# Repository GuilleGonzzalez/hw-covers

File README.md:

# Covers

## Description

'Covers' is a PCB designed to control x5 covers with 10 relays and automatize it with [Home Assistant](https://www.home-assistant.io/).

Firmware used in this device is [tasmota](https://tasmota.github.io/docs/), an open source firmware for ESP devices.

## Power supply

The board is powered with a 230VAC power supply.

## Microprocessor

Espressif [ESP32-S3-WROOM](https://www.espressif.com/en/products/modules) module.

## LEDs

2 user LEDs. Functionality to define

## Relay Mode

**Circuit Safe**
* Relay1: ON/OFF
* Relay2: UP/DOWN

A RC snubber has been added for all relays to absorb voltage spikes

## Tasmota config

An example template will be uploaded when configured.

## Pin assignment

| PIN     | Func    |
| ------- | ------- |
| OUT1    | GPIO12  |
| DIR1    | GPIO11  |
| OUT2    | GPIO14  |
| DIR2    | GPIO13  |
| OUT3    | GPIO47  |
| DIR3    | GPIO21  |
| OUT4    | GPIO18  |
| DIR4    | GPIO08  |
| OUT5    | GPIO16  |
| DIR5    | GPIO17  |
| 1IN1    | GPIO09  |
| 1IN2    | GPIO10  |
| 2IN1    | GPIO19  |
| 2IN2    | GPIO20  |
| 3IN1    | GPIO40  |
| 3IN2    | GPIO39  |
| 4IN1    | GPIO42  |
| 4IN2    | GPIO41  |
| 5IN1    | GPIO01  |
| 5IN2    | GPIO02  |
| IR      | GPIO06  |
| LED1    | GPIO15  |
| LED2    | GPIO07  |
| EXT1    | GPIO04  |
| EXT2    | GPIO05  |

## Enclosure

* Custom made.

## Changelog

All notable changes to this project will be documented in this section.

The format is based on [Keep a Changelog](https://keepachangelog.com/en/1.0.0/)

### [Unreleased]

### [2.1.0] - 2026-03-09

Fix some 2.0.0 rev issues

#### Added

* Add RC-snubbers values
* Add IR base resistor
* Add via stiching in regulator for power disipation

#### Fixed

* Fix L/N label text
* Isolate 230V AC lines from 5V DC lines

#### Changed

* Change relays transistor base from 1k to 470ohm

### [2.0.0] - 2026-03-08

Solved relay issue

#### Added

* Add RC snubbers
* Add schematic hierarchicals sheets

#### Fixed

* Change relays from 5A to 10A
* Change relay config to hardware-safe (output and direction) using form-C relays

#### Changed

* Change input resistor from 10k to 1k5
* Change ESP pin assignment

### [1.1.0] - 2025-02-28

Bug fixes

#### Added

* IR LED resistor value calculated: 180ohm

#### Fixed

* Relay NO/NC bug
* 1N4448W diode package fixed: SOD-123

#### Changed

* Better relays: 5A instead 3A, better pinout for clearance, thiner footprint
* HiLink symbol
* Rounded corners
* Components size: R/C 0603 instead 0402
* Inputs/outputs order: from left to right 1-5 in both cases

### [1.0.0] - 2025-02-05

First release

#### Added

* x5 covers

[Unreleased]: https://github.com/GuilleGonzzalez/hw-covers
[1.0.0]: https://github.com/GuilleGonzzalez/hw-covers/tree/v1.0.0
[1.1.0]: https://github.com/GuilleGonzzalez/hw-covers/tree/v1.1.0
[2.0.0]: https://github.com/GuilleGonzzalez/hw-covers/tree/v2.0.0
[2.1.0]: https://github.com/GuilleGonzzalez/hw-covers/tree/v2.1.0

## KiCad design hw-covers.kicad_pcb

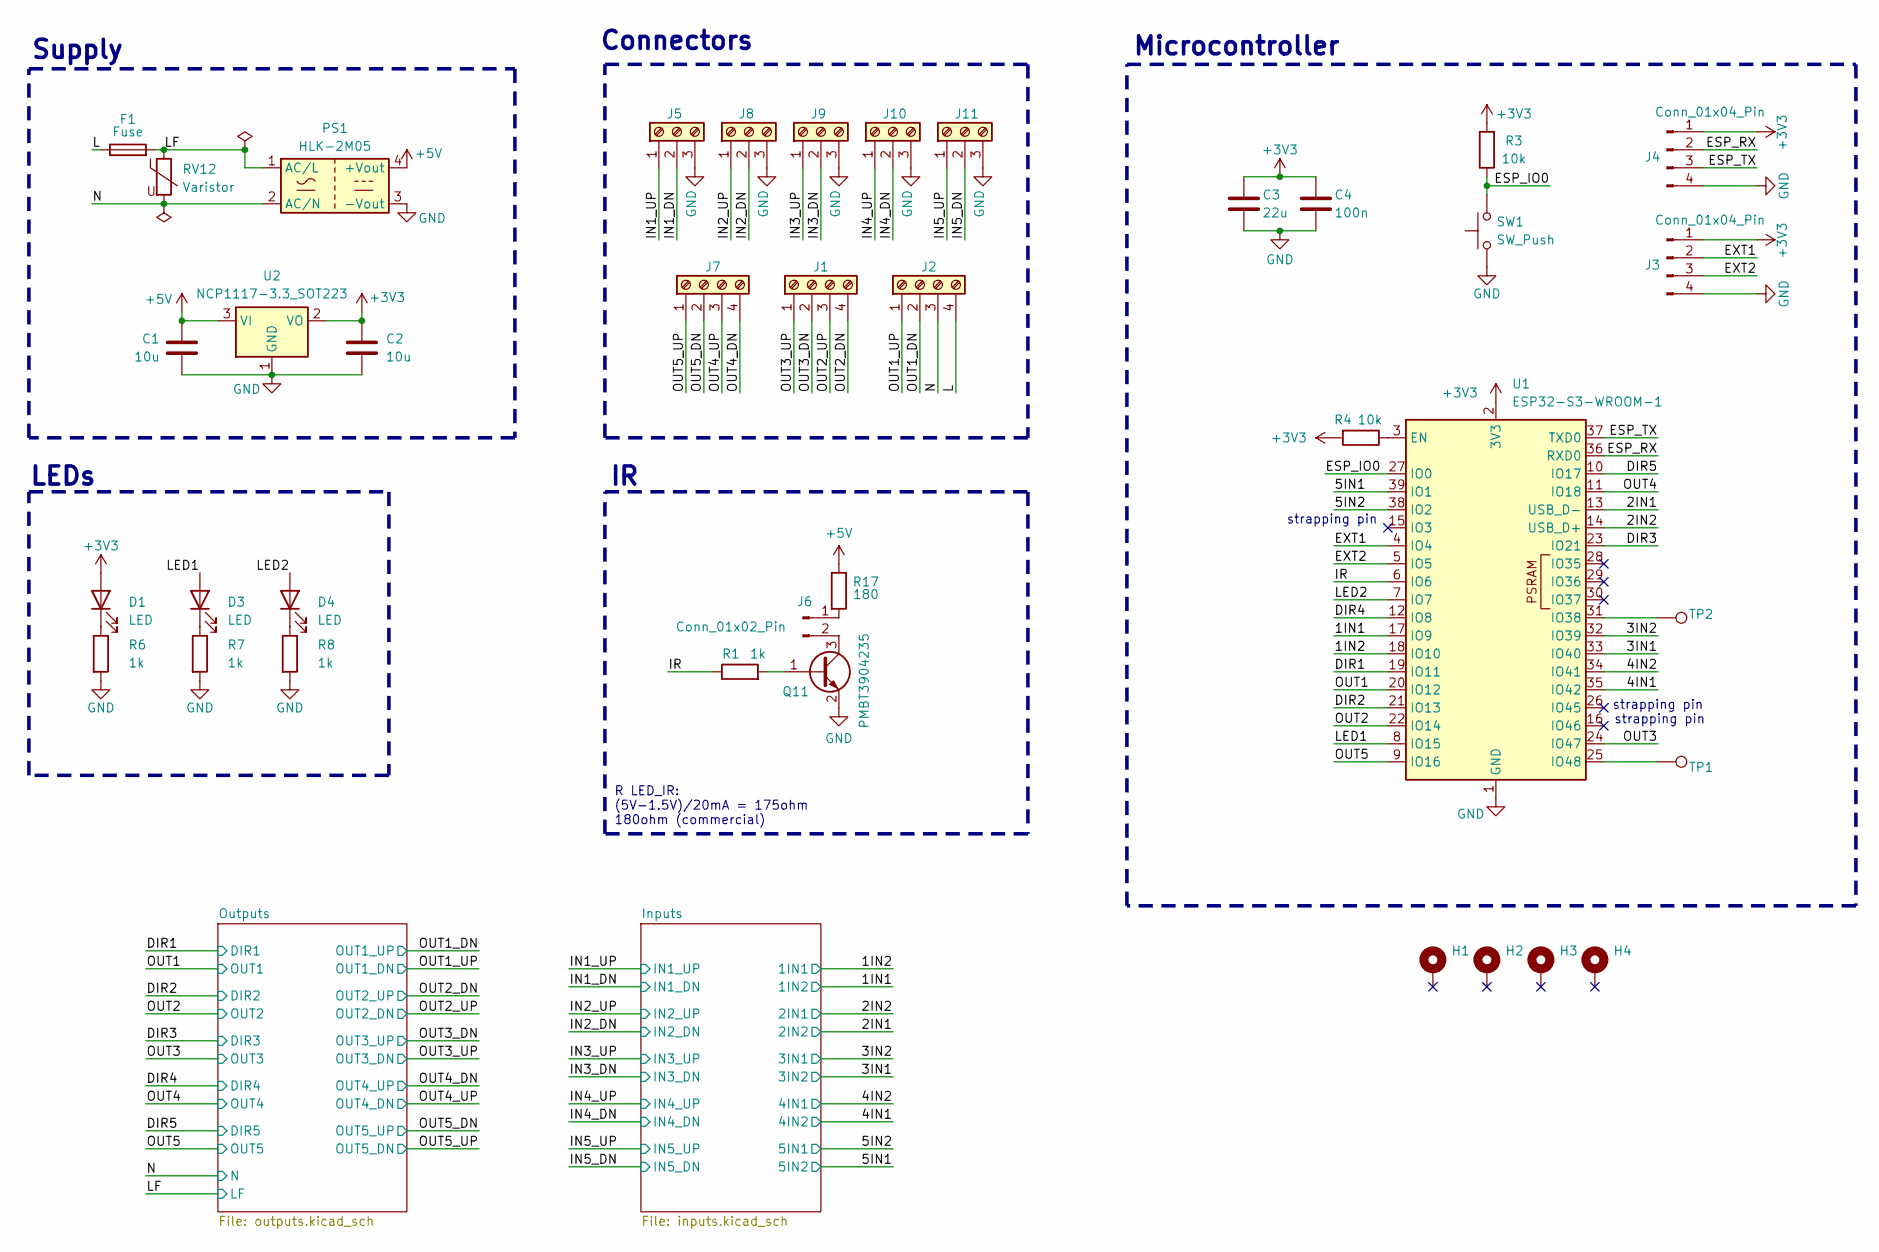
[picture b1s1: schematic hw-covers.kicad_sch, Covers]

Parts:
C1, C2: 10u; C_0805_2012Metric
C3: 22u; C_0805_2012Metric
C4: 100n; C_0603_1608Metric
D1, D3, D4: LED; LED_0603_1608Metric
F1: Fuse; Fuse_2512_6332Metric
H1, H2, H3, H4: MountingHole_3.2mm_M3_Pad
J1, J2, J7: Screw_Terminal_01x04; PhoenixContact_MSTBA_2,5_4-G-5,08_1x04_P5.08mm_Horizontal
J3, J4: Conn_01x04_Pin; PinHeader_1x04_P2.54mm_Vertical
J5, J8, J9, J10, J11: Screw_Terminal_01x03; PhoenixContact_MC_1,5_3-G-3.81_1x03_P3.81mm_Horizontal
J6: Conn_01x02_Pin; PinHeader_1x02_P2.54mm_Vertical
PS1: HLK-2M05; Converter_ACDC_Hi-Link_HLK-2Mxx
Q11: PMBT3904235; SOT-23; Manufacturer_PN PMBT3904,235
R1, R6, R7, R8: 1k; R_0603_1608Metric
R3, R4: 10k; R_0603_1608Metric
R17: 180; R_0603_1608Metric
RV12: Varistor; RV_Disc_D12mm_W4.5mm_P7.5mm
SW1: SW_Push; SW_SPST_PTS810
TP1, TP2: TestPoint; TestPoint_Pad_D1.5mm
U1: ESP32-S3-WROOM-1
U2: NCP1117-3.3_SOT223; SOT-223-3_TabPin2

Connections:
+3V3: C2.1, C3.1, C4.1, D1.2 (A), J3.1, J4.1, R3.2, R4.2, U1.2 (3V3), U2.2 (VO); also elsewhere on the board
+5V: C1.1, PS1.4 (+Vout), R17.1, U2.3 (VI); also elsewhere on the board
/1IN1: U1.17 (IO9); also elsewhere on the board
/1IN2: U1.18 (IO10); also elsewhere on the board
/2IN1: U1.13 (USB_D-); also elsewhere on the board
/2IN2: U1.14 (USB_D+); also elsewhere on the board
/3IN1: U1.33 (IO40); also elsewhere on the board
/3IN2: U1.32 (IO39); also elsewhere on the board
/4IN1: U1.35 (IO42); also elsewhere on the board
/4IN2: U1.34 (IO41); also elsewhere on the board
/5IN1: U1.39 (IO1); also elsewhere on the board
/5IN2: U1.38 (IO2); also elsewhere on the board
/DIR1: U1.19 (IO11); also elsewhere on the board
/DIR2: U1.21 (IO13); also elsewhere on the board
/DIR3: U1.23 (IO21); also elsewhere on the board
/DIR4: U1.12 (IO8); also elsewhere on the board
/DIR5: U1.10 (IO17); also elsewhere on the board
/ESP_IO0: R3.1, SW1.2, U1.27 (IO0)
/ESP_RX: J4.2, U1.36 (RXD0)
/ESP_TX: J4.3, U1.37 (TXD0)
/EXT1: J3.2, U1.4 (IO4)
/EXT2: J3.3, U1.5 (IO5)
/IN1_DN: J5.2; also elsewhere on the board
/IN1_UP: J5.1; also elsewhere on the board
/IN2_DN: J8.2; also elsewhere on the board
/IN2_UP: J8.1; also elsewhere on the board
/IN3_DN: J9.2; also elsewhere on the board
/IN3_UP: J9.1; also elsewhere on the board
/IN4_DN: J10.2; also elsewhere on the board
/IN4_UP: J10.1; also elsewhere on the board
/IN5_DN: J11.2; also elsewhere on the board
/IN5_UP: J11.1; also elsewhere on the board
/IR: R1.1, U1.6 (IO6)
/L: F1.1, J2.4
/LED1: D3.2 (A), U1.8 (IO15)
/LED2: D4.2 (A), U1.7 (IO7)
/LF: F1.2, PS1.1 (AC/L), RV12.1; also elsewhere on the board
/N: J2.3, PS1.2 (AC/N), RV12.2; also elsewhere on the board
/OUT1: U1.20 (IO12); also elsewhere on the board
/OUT1_DN: J2.2; also elsewhere on the board
/OUT1_UP: J2.1; also elsewhere on the board
/OUT2: U1.22 (IO14); also elsewhere on the board
/OUT2_DN: J1.4; also elsewhere on the board
/OUT2_UP: J1.3; also elsewhere on the board
/OUT3: U1.24 (IO47); also elsewhere on the board
/OUT3_DN: J1.2; also elsewhere on the board
/OUT3_UP: J1.1; also elsewhere on the board
/OUT4: U1.11 (IO18); also elsewhere on the board
/OUT4_DN: J7.4; also elsewhere on the board
/OUT4_UP: J7.3; also elsewhere on the board
/OUT5: U1.9 (IO16); also elsewhere on the board
/OUT5_DN: J7.2; also elsewhere on the board
/OUT5_UP: J7.1; also elsewhere on the board
GND: C1.2, C2.2, C3.2, C4.2, J3.4, J4.4, J5.3, J8.3, J9.3, J10.3, J11.3, PS1.3 (-Vout), Q11.2, R6.2, R7.2, R8.2, SW1.1, U1.1 (GND), U1.40 (GND), U1.41 (GND), U2.1 (GND); also elsewhere on the board
unnamed: D1.1 (K), R6.1
unnamed: D3.1 (K), R7.1
unnamed: D4.1 (K), R8.1
unnamed: J6.1, R17.2
unnamed: J6.2, Q11.3
unnamed: Q11.1, R1.2
unnamed: R4.1, U1.3 (EN)
unnamed: TP2.1, U1.31 (IO38)
unnamed: TP1.1, U1.25 (IO48)

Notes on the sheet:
Microcontroller
strapping pin
Supply
Connectors
R LED_IR: (5V-1.5V)/20mA = 175ohm 180ohm (commercial)
LEDs

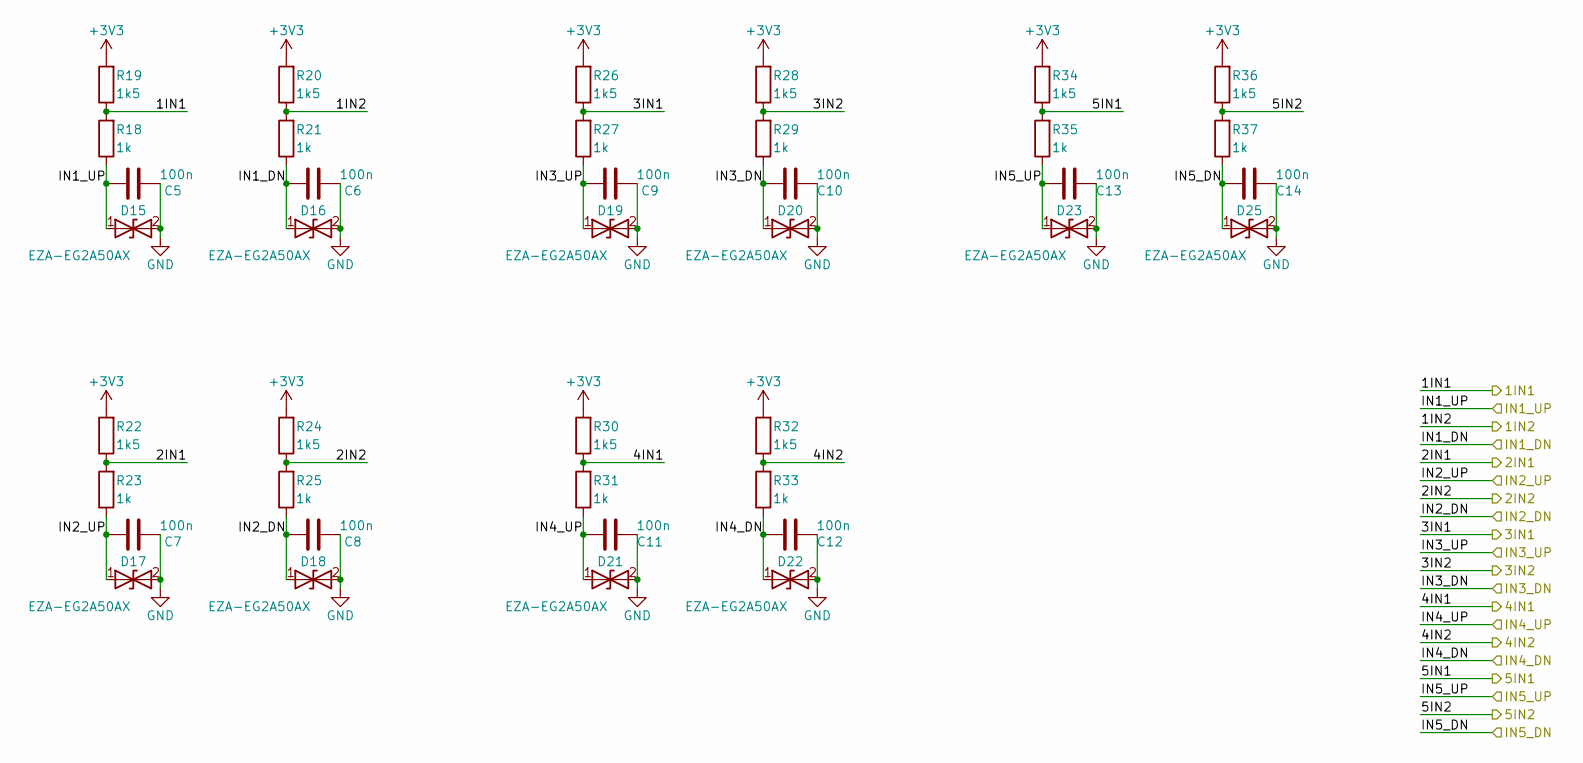
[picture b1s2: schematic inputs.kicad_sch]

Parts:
C5, C6, C7, C8, C9, C10, C11, C12, C13, C14: 100n; C_0603_1608Metric
D15, D16, D17, D18, D19, D20, D21, D22, D23, D25: EZA-EG2A50AX; EZAEG2A50AX; Manufacturer_Part_Number EZA-EG2A50AX; Mouser Part Number 667-EZA-EG2A50AX
R18, R21, R23, R25, R27, R29, R31, R33, R35, R37: 1k; R_0603_1608Metric
R19, R20, R22, R24, R26, R28, R30, R32, R34, R36: 1k5; R_0603_1608Metric

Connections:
+3V3: R19.2, R20.2, R22.2, R24.2, R26.2, R28.2, R30.2, R32.2, R34.2, R36.2; also elsewhere on the board
/1IN1: R20.1, R21.2; also elsewhere on the board
/1IN2: R18.2, R19.1; also elsewhere on the board
/2IN1: R24.1, R25.2; also elsewhere on the board
/2IN2: R22.1, R23.2; also elsewhere on the board
/3IN1: R28.1, R29.2; also elsewhere on the board
/3IN2: R26.1, R27.2; also elsewhere on the board
/4IN1: R32.1, R33.2; also elsewhere on the board
/4IN2: R30.1, R31.2; also elsewhere on the board
/5IN1: R36.1, R37.2; also elsewhere on the board
/5IN2: R34.1, R35.2; also elsewhere on the board
/IN1_DN: C6.1, D16.1 (A1), R21.1; also elsewhere on the board
/IN1_UP: C5.1, D15.1 (A1), R18.1; also elsewhere on the board
/IN2_DN: C8.1, D18.1 (A1), R25.1; also elsewhere on the board
/IN2_UP: C7.1, D17.1 (A1), R23.1; also elsewhere on the board
/IN3_DN: C10.1, D20.1 (A1), R29.1; also elsewhere on the board
/IN3_UP: C9.1, D19.1 (A1), R27.1; also elsewhere on the board
/IN4_DN: C12.1, D22.1 (A1), R33.1; also elsewhere on the board
/IN4_UP: C11.1, D21.1 (A1), R31.1; also elsewhere on the board
/IN5_DN: C14.1, D25.1 (A1), R37.1; also elsewhere on the board
/IN5_UP: C13.1, D23.1 (A1), R35.1; also elsewhere on the board
GND: C5.2, C6.2, C7.2, C8.2, C9.2, C10.2, C11.2, C12.2, C13.2, C14.2, D15.2 (A2), D16.2 (A2), D17.2 (A2), D18.2 (A2), D19.2 (A2), D20.2 (A2), D21.2 (A2), D22.2 (A2), D23.2 (A2), D25.2 (A2); also elsewhere on the board

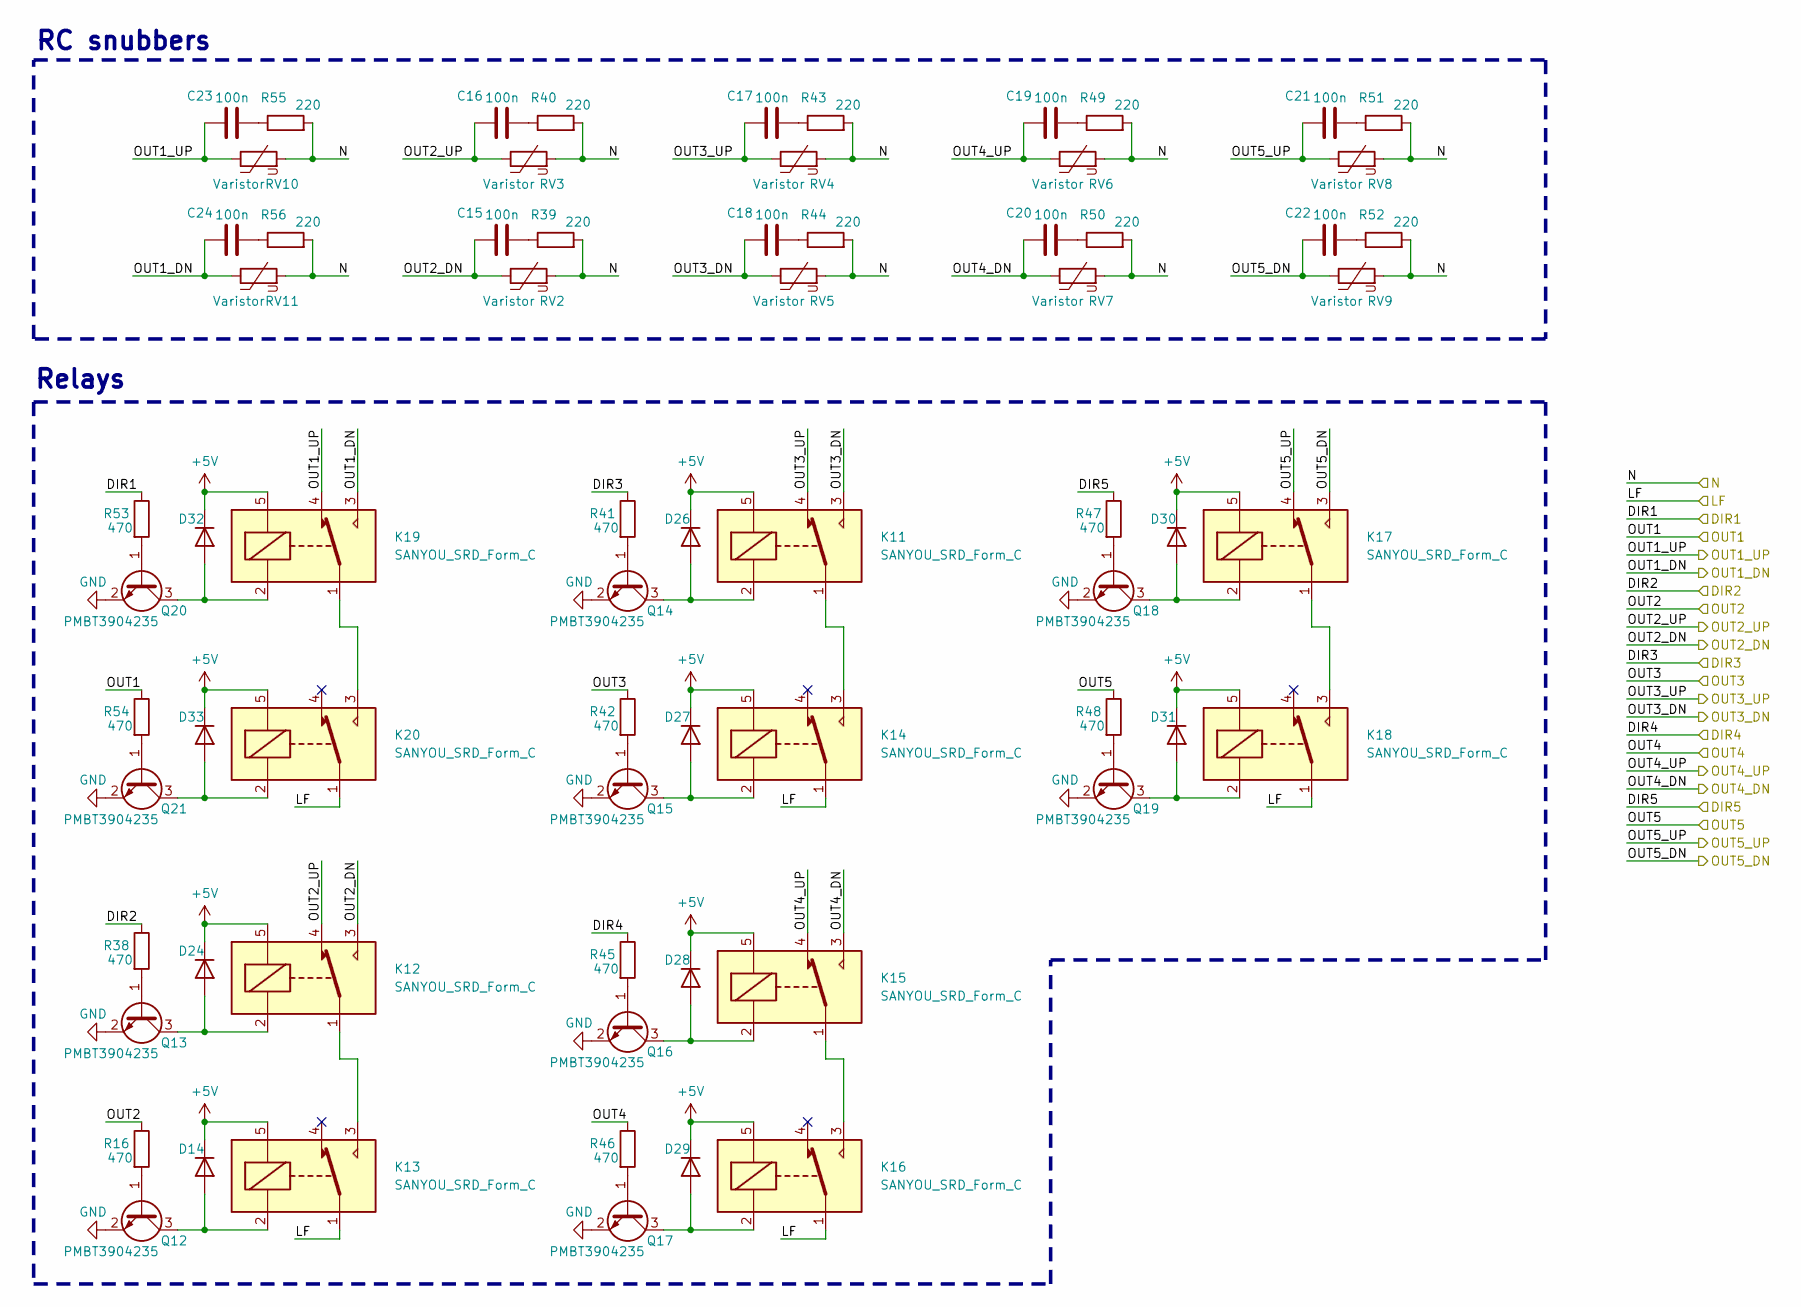
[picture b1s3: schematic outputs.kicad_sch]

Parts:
C15, C16, C17, C18, C19, C20, C21, C22, C23, C24: 100n; C_Rect_L18.0mm_W7.0mm_P15.00mm_FKS3_FKP3
D14, D24, D26, D27, D28, D29, D30, D31, D32, D33: 1N4448W; D_SOD-123
K11, K12, K13, K14, K15, K16, K17, K18, K19, K20: SANYOU_SRD_Form_C; Relay_SPDT_SANYOU_SRD_Series_Form_C
Q12, Q13, Q14, Q15, Q16, Q17, Q18, Q19, Q20, Q21: PMBT3904235; SOT-23; Manufacturer_PN PMBT3904,235
R16, R38, R41, R42, R45, R46, R47, R48, R53, R54: 470; R_0603_1608Metric
R39, R40, R43, R44, R49, R50, R51, R52, R55, R56: 220; R_Axial_DIN0614_L14.3mm_D5.7mm_P15.24mm_Horizontal
RV2, RV3, RV4, RV5, RV6, RV7, RV8, RV9, RV10, RV11: Varistor; RV_Disc_D12mm_W3.9mm_P7.5mm

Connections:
+5V: D14.1 (K), D24.1 (K), D26.1 (K), D27.1 (K), D28.1 (K), D29.1 (K), D30.1 (K), D31.1 (K), D32.1 (K), D33.1 (K), K11.5, K12.5, K13.5, K14.5, K15.5, K16.5, K17.5, K18.5, K19.5, K20.5; also elsewhere on the board
/DIR1: R53.1; also elsewhere on the board
/DIR2: R38.1; also elsewhere on the board
/DIR3: R41.1; also elsewhere on the board
/DIR4: R45.1; also elsewhere on the board
/DIR5: R47.1; also elsewhere on the board
/LF: K13.1, K14.1, K16.1, K18.1, K20.1; also elsewhere on the board
/N: R39.2, R40.2, R43.2, R44.2, R49.2, R50.2, R51.2, R52.2, R55.2, R56.2, RV2.2, RV3.2, RV4.2, RV5.2, RV6.2, RV7.2, RV8.2, RV9.2, RV10.2, RV11.2; also elsewhere on the board
/OUT1: R54.1; also elsewhere on the board
/OUT1_DN: C23.1, K19.4, RV10.1; also elsewhere on the board
/OUT1_UP: C24.1, K19.3, RV11.1; also elsewhere on the board
/OUT2: R16.1; also elsewhere on the board
/OUT2_DN: C16.1, K12.4, RV3.1; also elsewhere on the board
/OUT2_UP: C15.1, K12.3, RV2.1; also elsewhere on the board
/OUT3: R42.1; also elsewhere on the board
/OUT3_DN: C17.1, K11.4, RV4.1; also elsewhere on the board
/OUT3_UP: C18.1, K11.3, RV5.1; also elsewhere on the board
/OUT4: R46.1; also elsewhere on the board
/OUT4_DN: C19.1, K15.4, RV6.1; also elsewhere on the board
/OUT4_UP: C20.1, K15.3, RV7.1; also elsewhere on the board
/OUT5: R48.1; also elsewhere on the board
/OUT5_DN: C21.1, K17.4, RV8.1; also elsewhere on the board
/OUT5_UP: C22.1, K17.3, RV9.1; also elsewhere on the board
GND: Q12.2, Q13.2, Q14.2, Q15.2, Q16.2, Q17.2, Q18.2, Q19.2, Q20.2, Q21.2; also elsewhere on the board
unnamed: C15.2, R39.1
unnamed: C16.2, R40.1
unnamed: C17.2, R43.1
unnamed: C18.2, R44.1
unnamed: C19.2, R49.1
unnamed: C20.2, R50.1
unnamed: C21.2, R51.1
unnamed: C22.2, R52.1
unnamed: C23.2, R55.1
unnamed: C24.2, R56.1
unnamed: D14.2 (A), K13.2, Q12.3
unnamed: D24.2 (A), K12.2, Q13.3
unnamed: D26.2 (A), K11.2, Q14.3
unnamed: D27.2 (A), K14.2, Q15.3
unnamed: D28.2 (A), K15.2, Q16.3
unnamed: D29.2 (A), K16.2, Q17.3
unnamed: D30.2 (A), K17.2, Q18.3
unnamed: D31.2 (A), K18.2, Q19.3
unnamed: D32.2 (A), K19.2, Q20.3
unnamed: D33.2 (A), K20.2, Q21.3
unnamed: K11.1, K14.3
unnamed: K12.1, K13.3
unnamed: K15.1, K16.3
unnamed: K17.1, K18.3
unnamed: K19.1, K20.3
unnamed: Q12.1, R16.2
unnamed: Q13.1, R38.2
unnamed: Q14.1, R41.2
unnamed: Q15.1, R42.2
unnamed: Q16.1, R45.2
unnamed: Q17.1, R46.2
unnamed: Q18.1, R47.2
unnamed: Q19.1, R48.2
unnamed: Q20.1, R53.2
unnamed: Q21.1, R54.2

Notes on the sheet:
Relays
RC snubbers

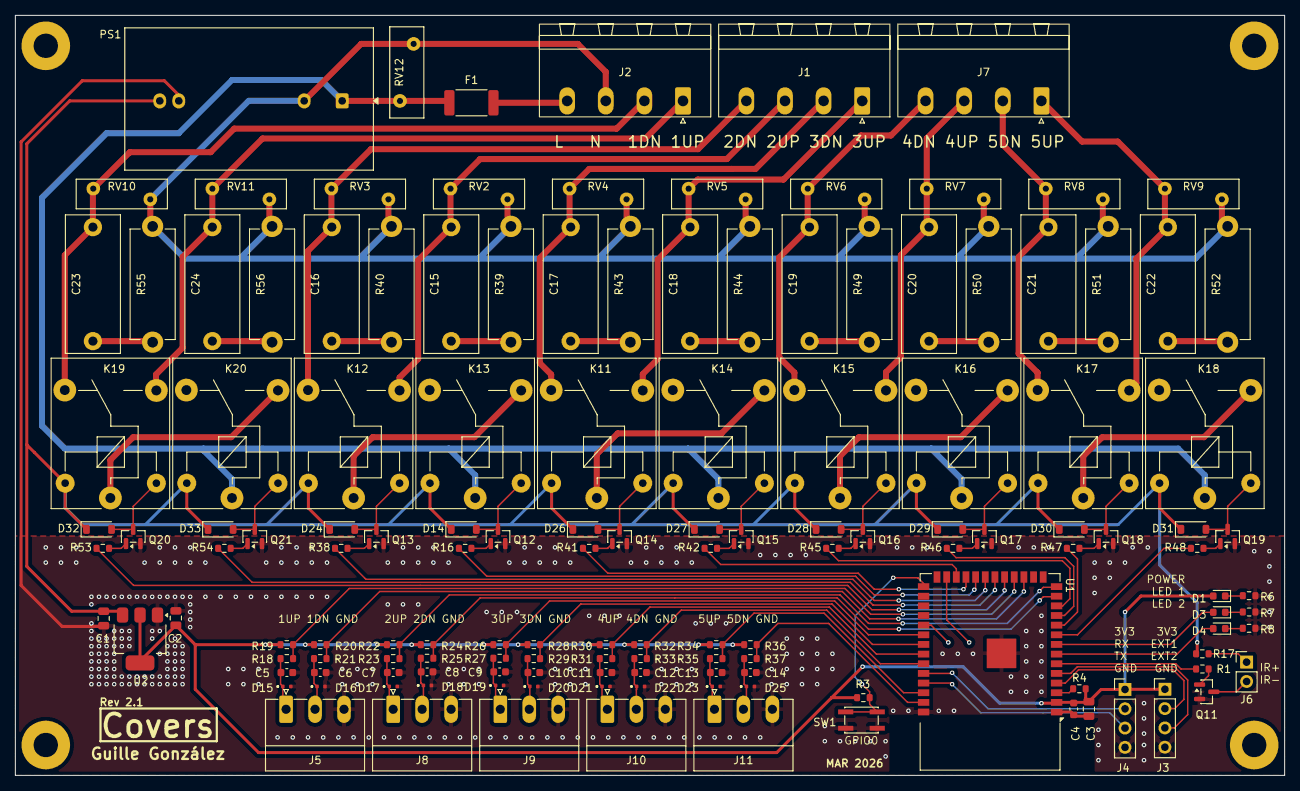
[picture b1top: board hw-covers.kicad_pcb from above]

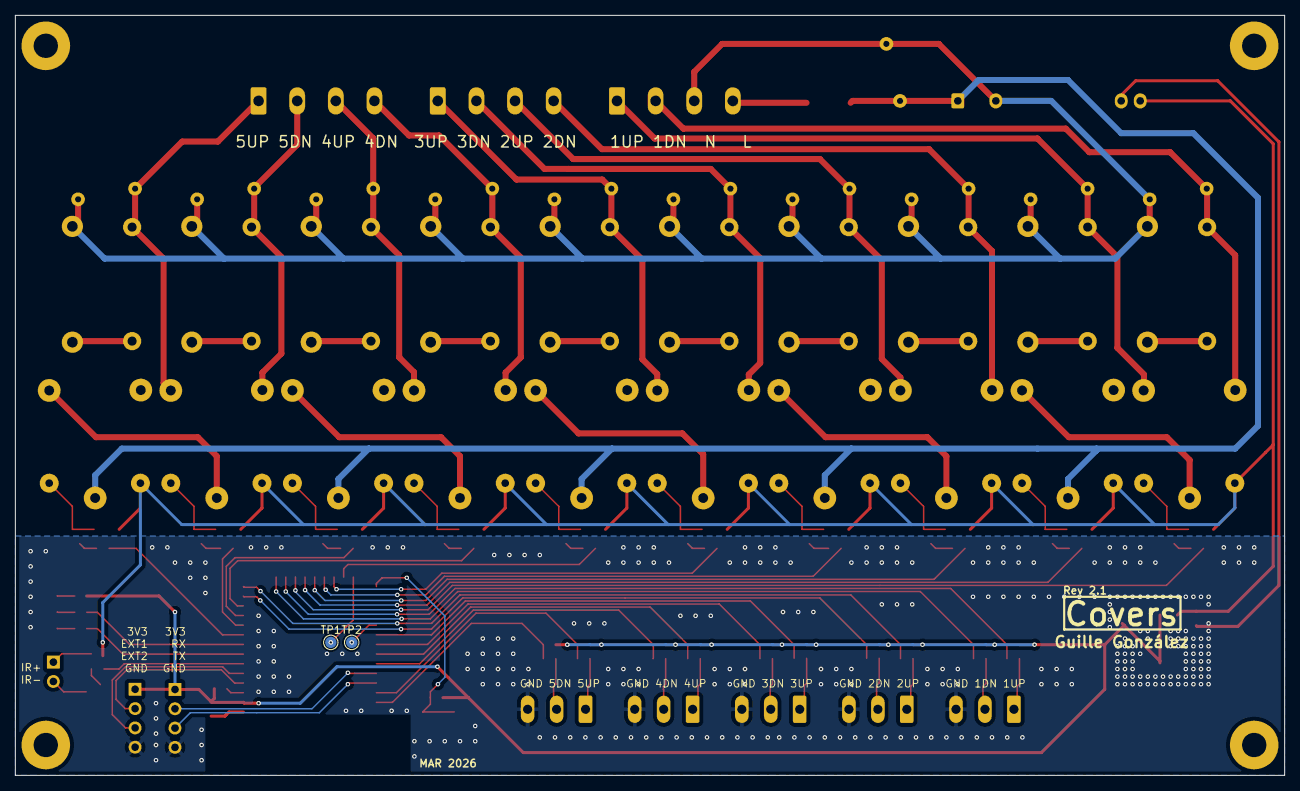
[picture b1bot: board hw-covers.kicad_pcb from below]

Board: 2 copper layers, 167.0 x 100.0 mm, 148 parts (2 on the bottom side), 98 nets.

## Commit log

2025-02-04 Finish sch and start with placement
2025-02-05 Release 1.0
2025-02-05 Change gerbers configuration
2025-02-28 Release 1.1
2025-02-28 Minor changes to release 1.1
2026-03-04 Update lib
2026-03-04 Sch update for rev 2
2026-03-05 Add placement
2026-03-06 Change in R values and routing test
2026-03-08 Finish routing
2026-03-08 Finish PCB
2026-03-08 Ready to release
2026-03-08 Fix changelog
2026-03-09 Release 2.1.0
